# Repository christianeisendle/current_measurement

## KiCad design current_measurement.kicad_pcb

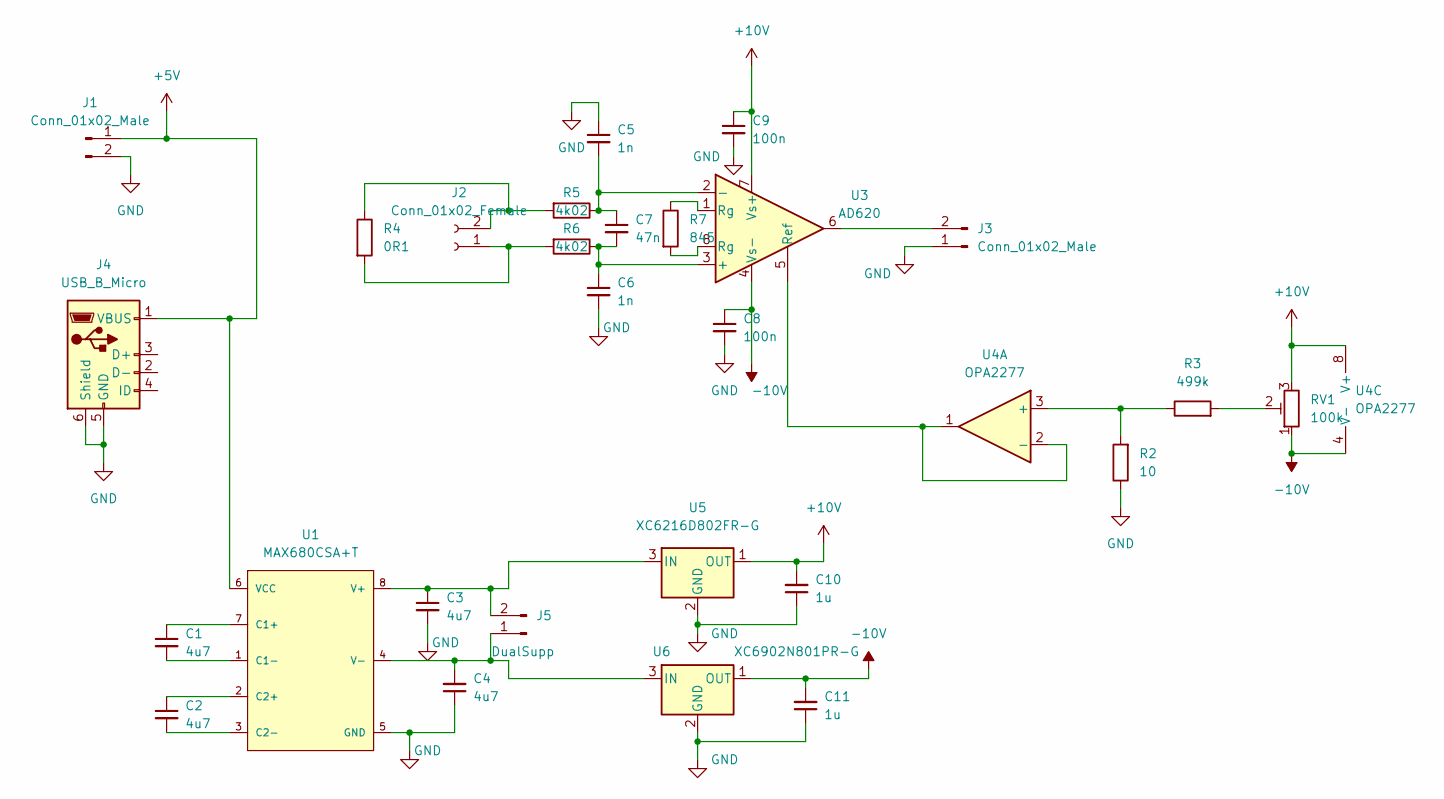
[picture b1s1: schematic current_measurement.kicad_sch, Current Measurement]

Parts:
C1, C2, C3, C4: 4u7; C_1210_3225Metric
C5, C6: 1n; C_0402_1005Metric_Pad0.74x0.62mm_HandSolder
C7: 47n; C_0402_1005Metric_Pad0.74x0.62mm_HandSolder
C8, C9: 100n; C_0603_1608Metric
C10, C11: 1u; C_0402_1005Metric_Pad0.74x0.62mm_HandSolder
J1, J3: Conn_01x02_Male; PinHeader_1x02_P2.54mm_Vertical
J2: Conn_01x02_Female; PinSocket_1x02_P2.54mm_Vertical
J4: USB_B_Micro; USB_Micro-B_Amphenol_10104110_Horizontal
J5: DualSupp; PinHeader_1x02_P2.54mm_Vertical
R2: 10; R_0402_1005Metric_Pad0.72x0.64mm_HandSolder
R3: 499k; R_0402_1005Metric_Pad0.72x0.64mm_HandSolder
R4: 0R1; R_2512_6332Metric
R5, R6: 4k02; R_0402_1005Metric_Pad0.72x0.64mm_HandSolder
R7: 845; R_0402_1005Metric_Pad0.72x0.64mm_HandSolder
RV1: 100k; Potentiometer_Bourns_3386C_Horizontal
U1: MAX680CSA+T; SOIC-8_3.9x4.9mm_P1.27mm; negative voltage availa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 true; output voltage 12V; mouser part number 700-MAX680CSAT; digikey description IC REG SWTCHD CAP INV 10MA 8SOIC
U3: AD620; SOIC-8_3.9x4.9mm_P1.27mm
U4: OPA2277; SOIC-8_3.9x4.9mm_P1.27mm
U5: XC6216D802FR-G; SOT-223-3_TabPin2
U6: XC6902N801PR-G; SOT-223-3_TabPin2

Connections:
+5V: J1.1, J4.1 (VBUS), U1.6 (VCC)
+10V: C9.1, C10.2, RV1.3, U3.7 (Vs+), U4.8 (V+), U5.1 (OUT)
-10V: C8.1, C11.2, RV1.1, U3.4 (Vs-), U4.4 (V-), U6.1 (OUT)
GND: C3.2, C4.1, C5.1, C6.2, C8.2, C9.2, C10.1, C11.1, J1.2, J3.1, J4.5 (GND), J4.6 (Shield), R2.1, U1.5 (GND), U5.2 (GND), U6.2 (GND)
unnamed: C1.1, U1.7 (C1+)
unnamed: C1.2, U1.1 (C1-)
unnamed: C2.1, U1.2 (C2+)
unnamed: C2.2, U1.3 (C2-)
unnamed: C3.1, J5.2, U1.8 (V+), U5.3 (IN)
unnamed: C5.2, C7.1, R5.1, U3.2 (-)
unnamed: C6.1, C7.2, R6.1, U3.3 (+)
unnamed: J2.1, R4.2, R6.2
unnamed: J2.2, R4.1, R5.2
unnamed: J3.2, U3.6
unnamed: R2.2, R3.1, U4.3 (+)
unnamed: R3.2, RV1.2
unnamed: R7.1, U3.1 (Rg)
unnamed: R7.2, U3.8 (Rg)
unnamed: C4.2, J5.1, U1.4 (V-), U6.3 (IN)
unnamed: U3.5 (Ref), U4.1, U4.2 (-)

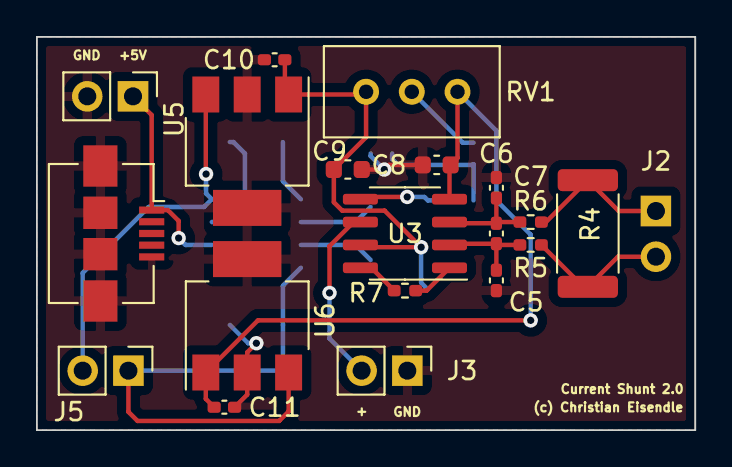
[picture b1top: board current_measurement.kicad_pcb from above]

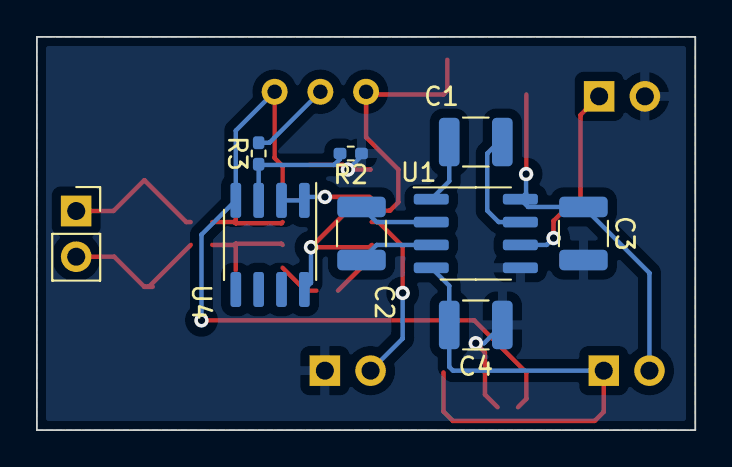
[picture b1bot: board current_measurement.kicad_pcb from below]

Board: 2 copper layers, 36.6 x 21.8 mm, 28 parts (9 on the bottom side), 20 nets.

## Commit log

2022-12-01 Initial commit of current measurement adapter
2022-12-01 Add pdf export of schematic
2022-12-01 Add gerber files for v1.0
2022-12-01 v1.1: SOC package for MAX680
2022-12-15 Current Shunt 2.0
